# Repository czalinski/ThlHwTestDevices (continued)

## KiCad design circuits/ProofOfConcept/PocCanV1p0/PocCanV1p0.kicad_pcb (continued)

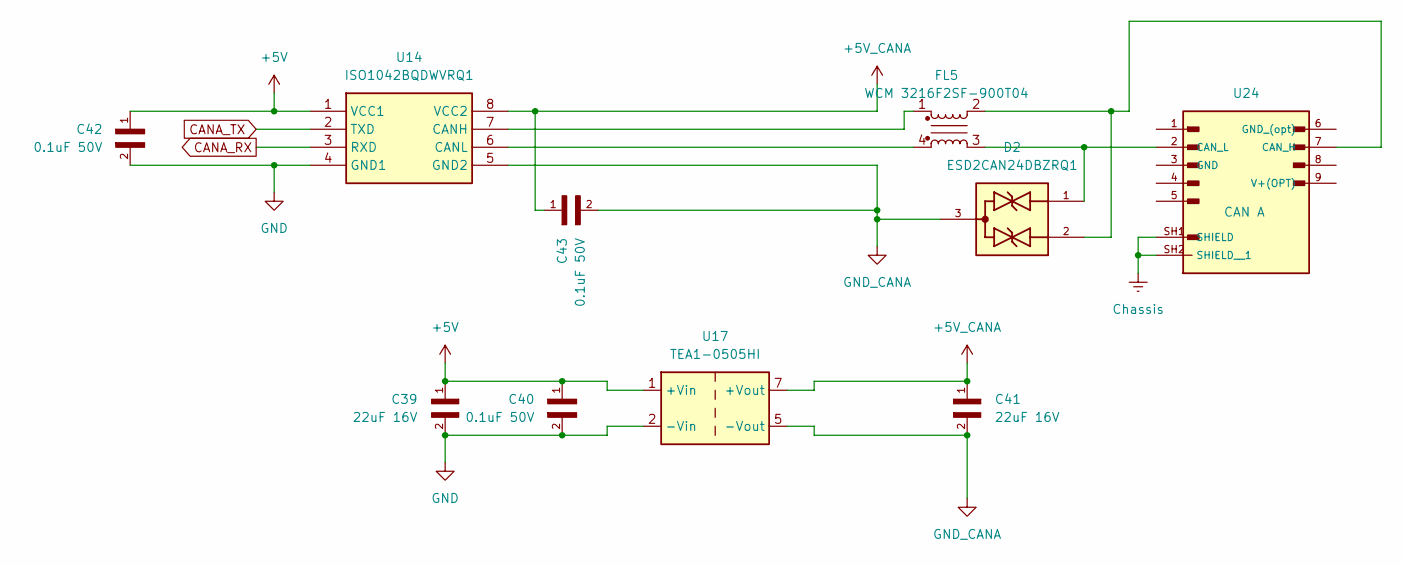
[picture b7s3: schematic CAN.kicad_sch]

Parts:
C39, C41: 22uF 16V; CAPC3216X95N
C40, C42, C43: 0.1uF 50V; CAPC2012X70
D2: ESD2CAN24DBZRQ1; SOT95P237X112-3N; PARTREV C
FL5: WCM 3216F2SF-900T04; WCM 3216F2SF-900T04-1206
U14: ISO1042BQDWVRQ1; SOIC127P1150X280-8N; Manufacturer_Part_Number ISO1042BQDWVRQ1; Mouser Part Number 595-ISO1042BQDWVRQ1
U17: TEA1-0505HI; Converter_DCDC_TRACO_TEA1-xxxxHI_THT
U24: CAN A; ASSMANN_A-DS_09_A_KG-T2S

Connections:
+5V: C39.1, C40.1, C42.1, U14.1 (VCC1), U17.1 (+Vin); also elsewhere on the board
+5V_CANA: C41.1, C43.1, U14.8 (VCC2), U17.7 (+Vout)
CANA_RX: U14.3 (RXD); also elsewhere on the board
CANA_TX: U14.2 (TXD); also elsewhere on the board
Chassis: U24.SH1 (SHIELD), U24.SH2 (SHIELD__1); also elsewhere on the board
GND: C39.2, C40.2, C42.2, U14.4 (GND1), U17.2 (-Vin); also elsewhere on the board
GND_CANA: C41.2, C43.2, D2.3, U14.5 (GND2), U17.5 (-Vout)
unnamed: FL5.1, U14.7 (CANH)
unnamed: FL5.4, U14.6 (CANL)
unnamed: D2.2, FL5.2, U24.7 (CAN_H)
unnamed: D2.1, FL5.3, U24.2 (CAN_L)

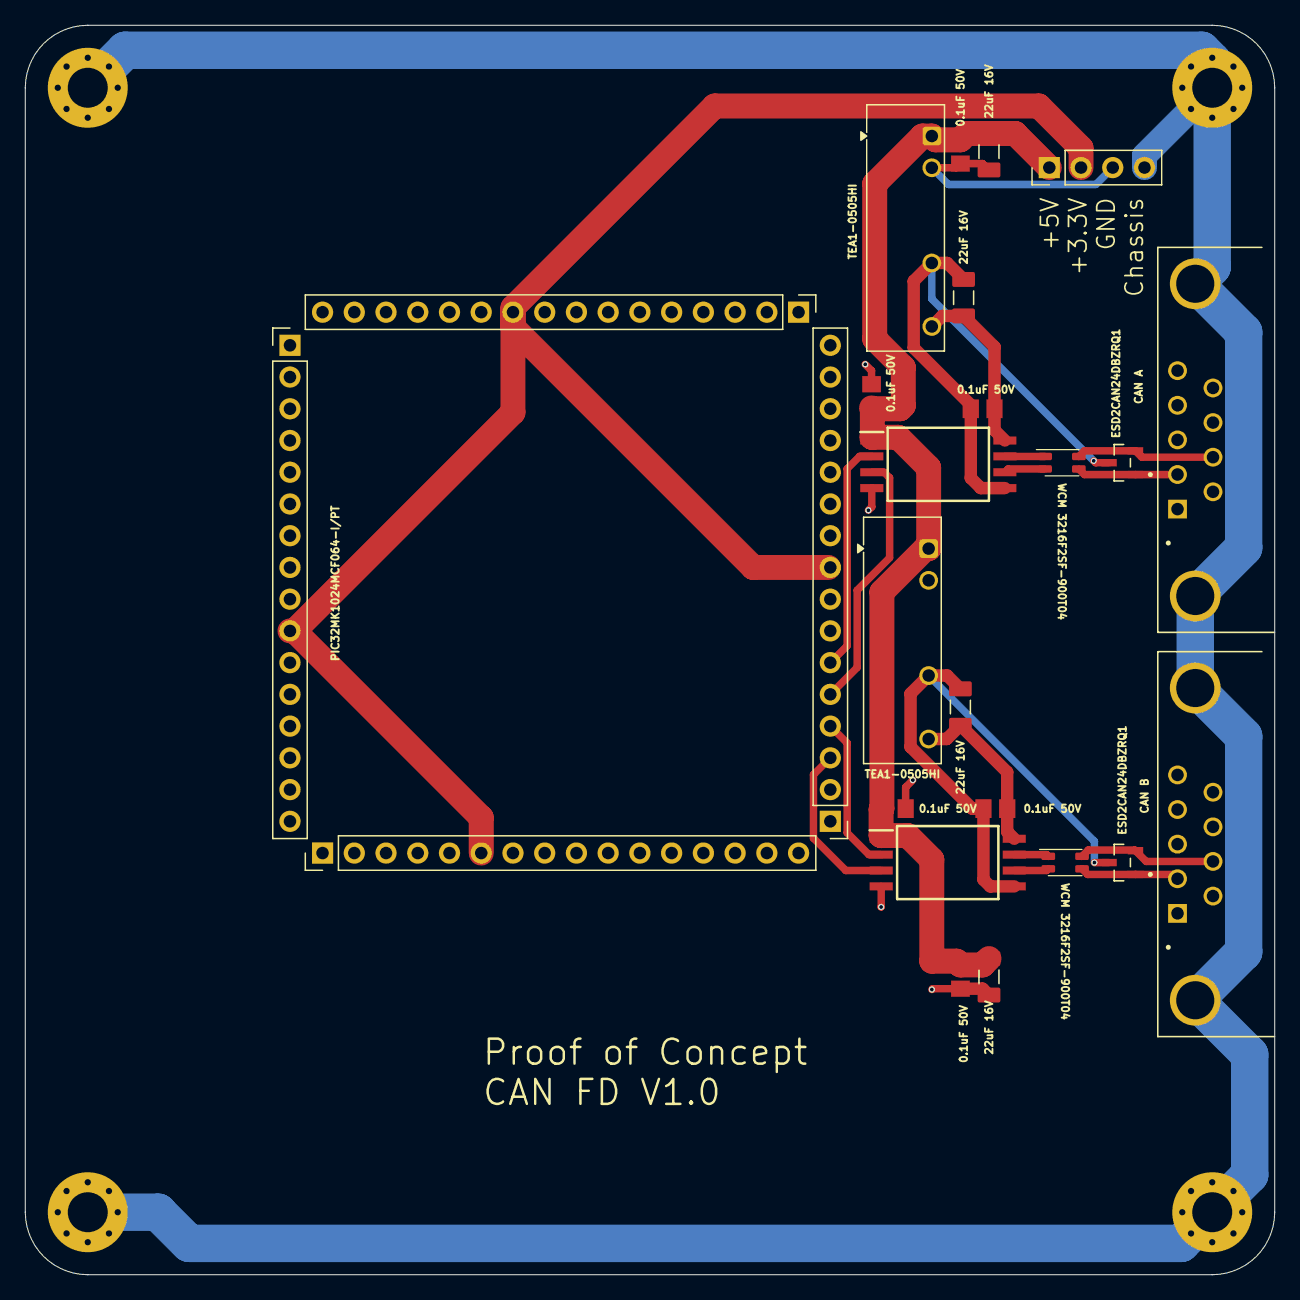
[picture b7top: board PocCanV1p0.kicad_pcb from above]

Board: 2 copper layers, 100.0 x 100.0 mm, 26 parts (0 on the bottom side), 20 nets.

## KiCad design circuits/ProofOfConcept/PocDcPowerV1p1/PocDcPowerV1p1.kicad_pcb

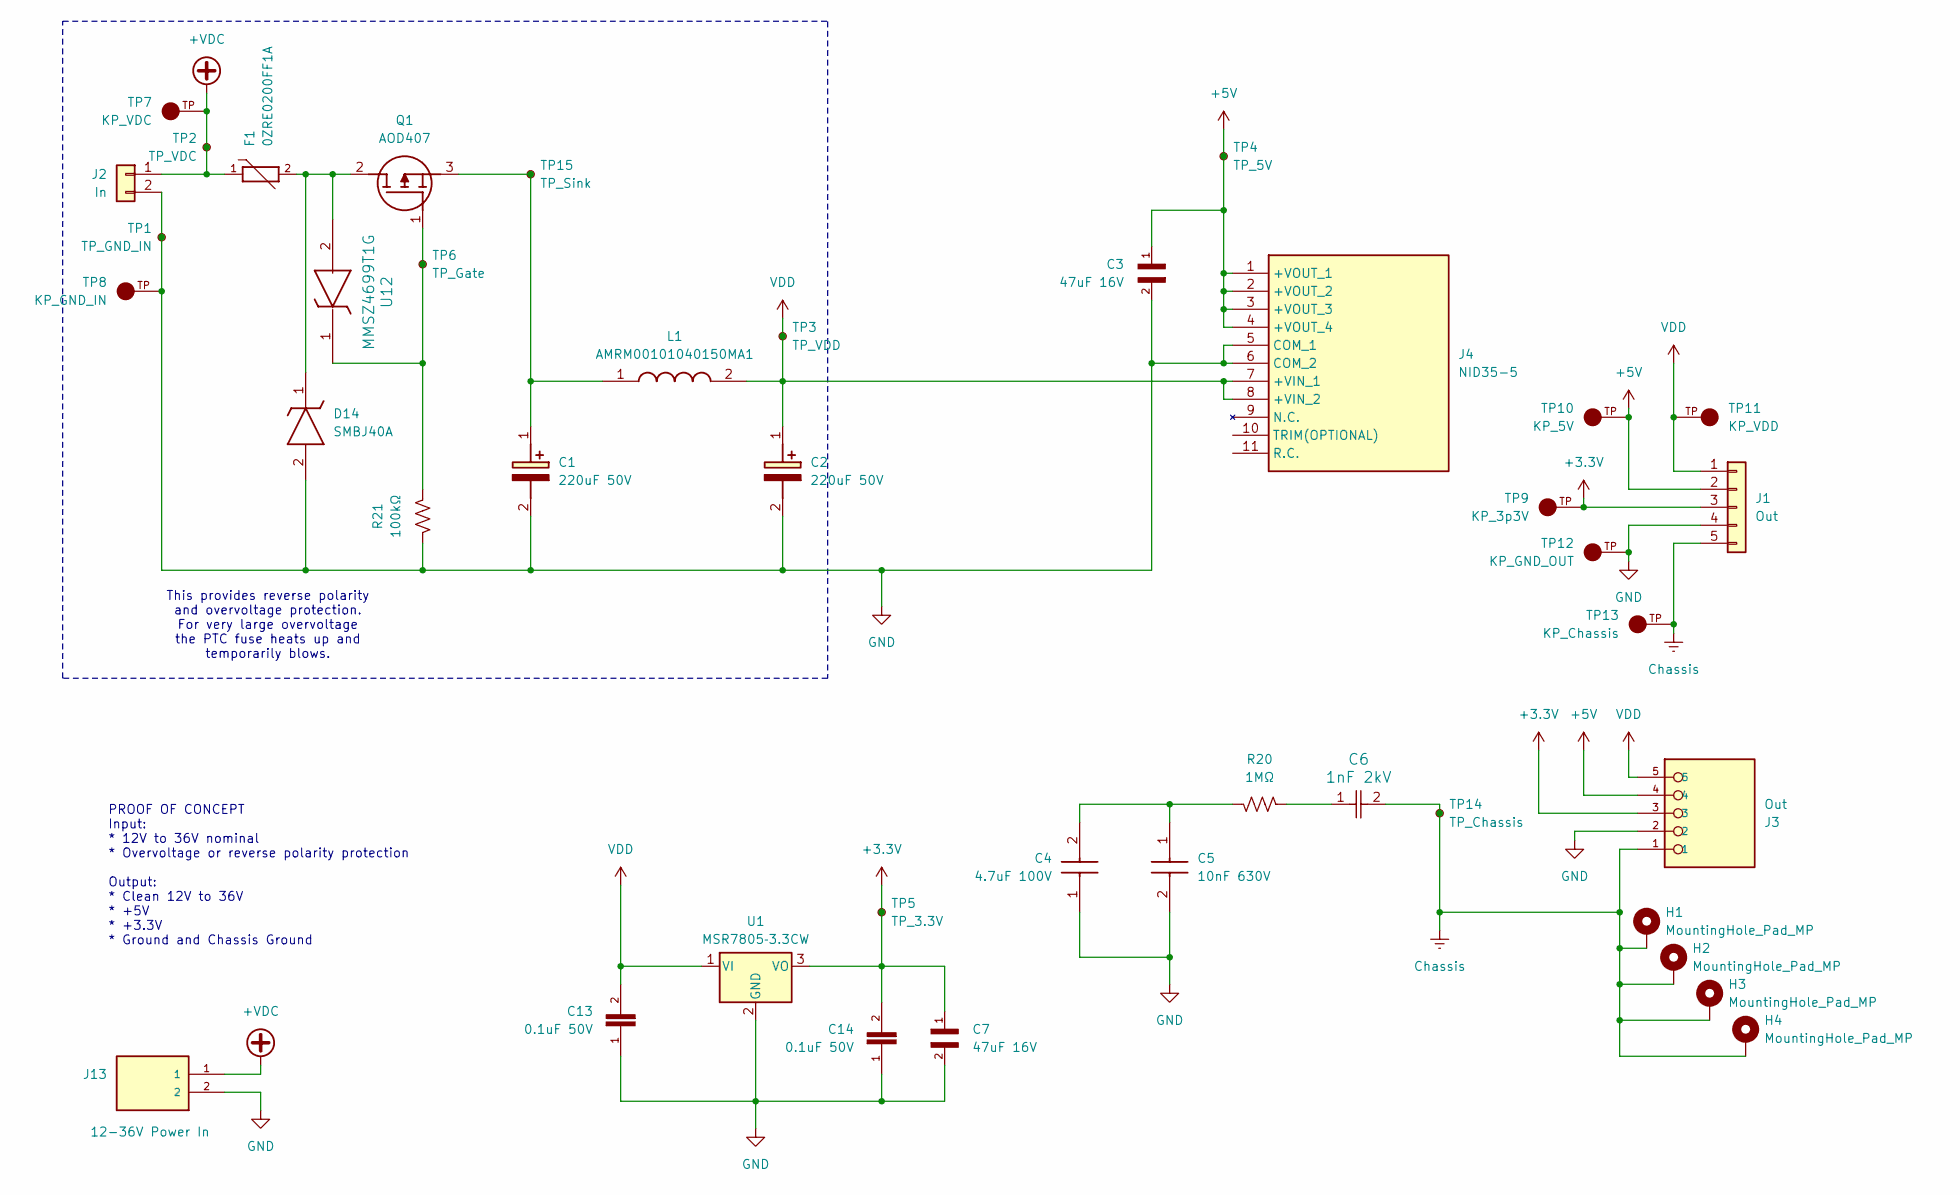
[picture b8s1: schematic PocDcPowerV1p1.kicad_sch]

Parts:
C1, C2: 220uF 50V; CAPPRD500W60D1025H1750; Manufacturer_Part_Number UHE1H221MPD; Mouser Part Number 647-UHE1H221MPD
C3, C7: 47uF 16V; CAPC3225X270N
C4: 4.7uF 100V; GRM31x; Manufacturer_Part_Number GRM31CC72A475ME11K; Mouser Part Number 81-GRM31CC72A475ME1K
C5: 10nF 630V; CAPC3216X135N; Manufacturer_Part_Number 1206B103K631CT
C6: 1nF 2kV; CAPC3216X170N
C13, C14: 0.1uF 50V; CAPC2012X70
D14: SMBJ40A; DIOM5436X265N; Manufacturer_Part_Number SMBJ40A
F1: 0ZRE0200FF1A; FUSRR1020W81L2490T610H3380; PARTREV Apr2023
H1, H2, H3, H4: MountingHole_Pad_MP; MountingHole_3.2mm_M3_Pad_Via
J1: Out; PinHeader_1x05_P2.54mm_Vertical
J2: In; PinHeader_1x02_P2.54mm_Vertical
J3: Out; PHOENIX_1990038
J4: NID35-5; NID355; Manufacturer_Part_Number NID35-5; Mouser Part Number 709-NID35-5
J13: 12-36V Power In; CUI_TB005-762-02BE
L1: AMRM00101040150MA1; INDPM116102X400N; Manufacturer_Part_Number AMRM00101040150MA1
Q1: AOD407; Manufacturer_Part_Number AOD407
R20: 1MΩ; RES_1206
R21: 100kΩ; RES_1206
TP1: TP_GND_IN; TestPoint_Pad_D1.0mm
TP2: TP_VDC; TestPoint_Pad_D1.0mm
TP3: TP_VDD; TestPoint_Pad_D1.0mm
TP4: TP_5V; TestPoint_Pad_D1.0mm
TP5: TP_3.3V; TestPoint_Pad_D1.0mm
TP6: TP_Gate; TestPoint_Pad_D1.0mm
TP7: KP_VDC; KEYSTONE_4954_Slot; PARTREV B; DigiKey_Part_Number 36-4954-ND
TP8: KP_GND_IN; KEYSTONE_4954_Slot; PARTREV B; DigiKey_Part_Number 36-4954-ND
TP9: KP_3p3V; KEYSTONE_4954_Slot; PARTREV B; DigiKey_Part_Number 36-4954-ND
TP10: KP_5V; KEYSTONE_4954_Slot; PARTREV B; DigiKey_Part_Number 36-4954-ND
TP11: KP_VDD; KEYSTONE_4954_Slot; PARTREV B; DigiKey_Part_Number 36-4954-ND
TP12: KP_GND_OUT; KEYSTONE_4954_Slot; PARTREV B; DigiKey_Part_Number 36-4954-ND
TP13: KP_Chassis; KEYSTONE_4954_Slot; PARTREV B; DigiKey_Part_Number 36-4954-ND
TP14: TP_Chassis; TestPoint_Pad_D1.0mm
TP15: TP_Sink; TestPoint_Pad_D1.0mm
U1: MSR7805‑3.3CW; 3-SIP
U12: MMSZ4699T1G; SOD-123_ONS

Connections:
+3.3V: C7.1, C14.2, J1.3, J3.3, TP5.1 (1_1), TP9.TP, U1.3 (VO)
+5V: C3.1, J1.2, J3.4, J4.1 (+VOUT_1), J4.2 (+VOUT_2), J4.3 (+VOUT_3), J4.4 (+VOUT_4), TP4.1 (1_1), TP10.TP
+VDC: F1.1, J2.1, J13.1, TP2.1 (1_1), TP7.TP
Chassis: C6.2, H1.1 (MP_1), H2.1 (MP_1), H3.1 (MP_1), H4.1 (MP_1), J1.5, J3.1, TP13.TP, TP14.1 (1_1)
GND: C1.2 (-), C2.2 (-), C3.2, C4.1, C5.2, C7.2, C13.1, C14.1, D14.2 (A), J1.4, J2.2, J3.2, J4.5 (COM_1), J4.6 (COM_2), J13.2, R21.2, TP1.1 (1_1), TP8.TP, TP12.TP, U1.2 (GND)
unnamed: C1.1 (+), L1.1, Q1.3 (S), TP15.1 (1_1)
unnamed: C4.2, C5.1, R20.2
unnamed: C6.1, R20.1
unnamed: D14.1 (K), F1.2, Q1.2 (D), U12.2
unnamed: Q1.1 (G), R21.1, TP6.1 (1_1), U12.1
VDD: C2.1 (+), C13.2, J1.1, J3.5, J4.7 (+VIN_1), J4.8 (+VIN_2), L1.2, TP3.1 (1_1), TP11.TP, U1.1 (VI)

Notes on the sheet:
PROOF OF CONCEPT Input: * 12V to 36V nominal * Overvoltage or reverse polarity protection Output: * Clean 12V to 36V * +5V * +3.3V * Ground and Chassis Ground
This provides reverse polarity and overvoltage protection. For very large overvoltage the PTC fuse heats up and temporarily blows.

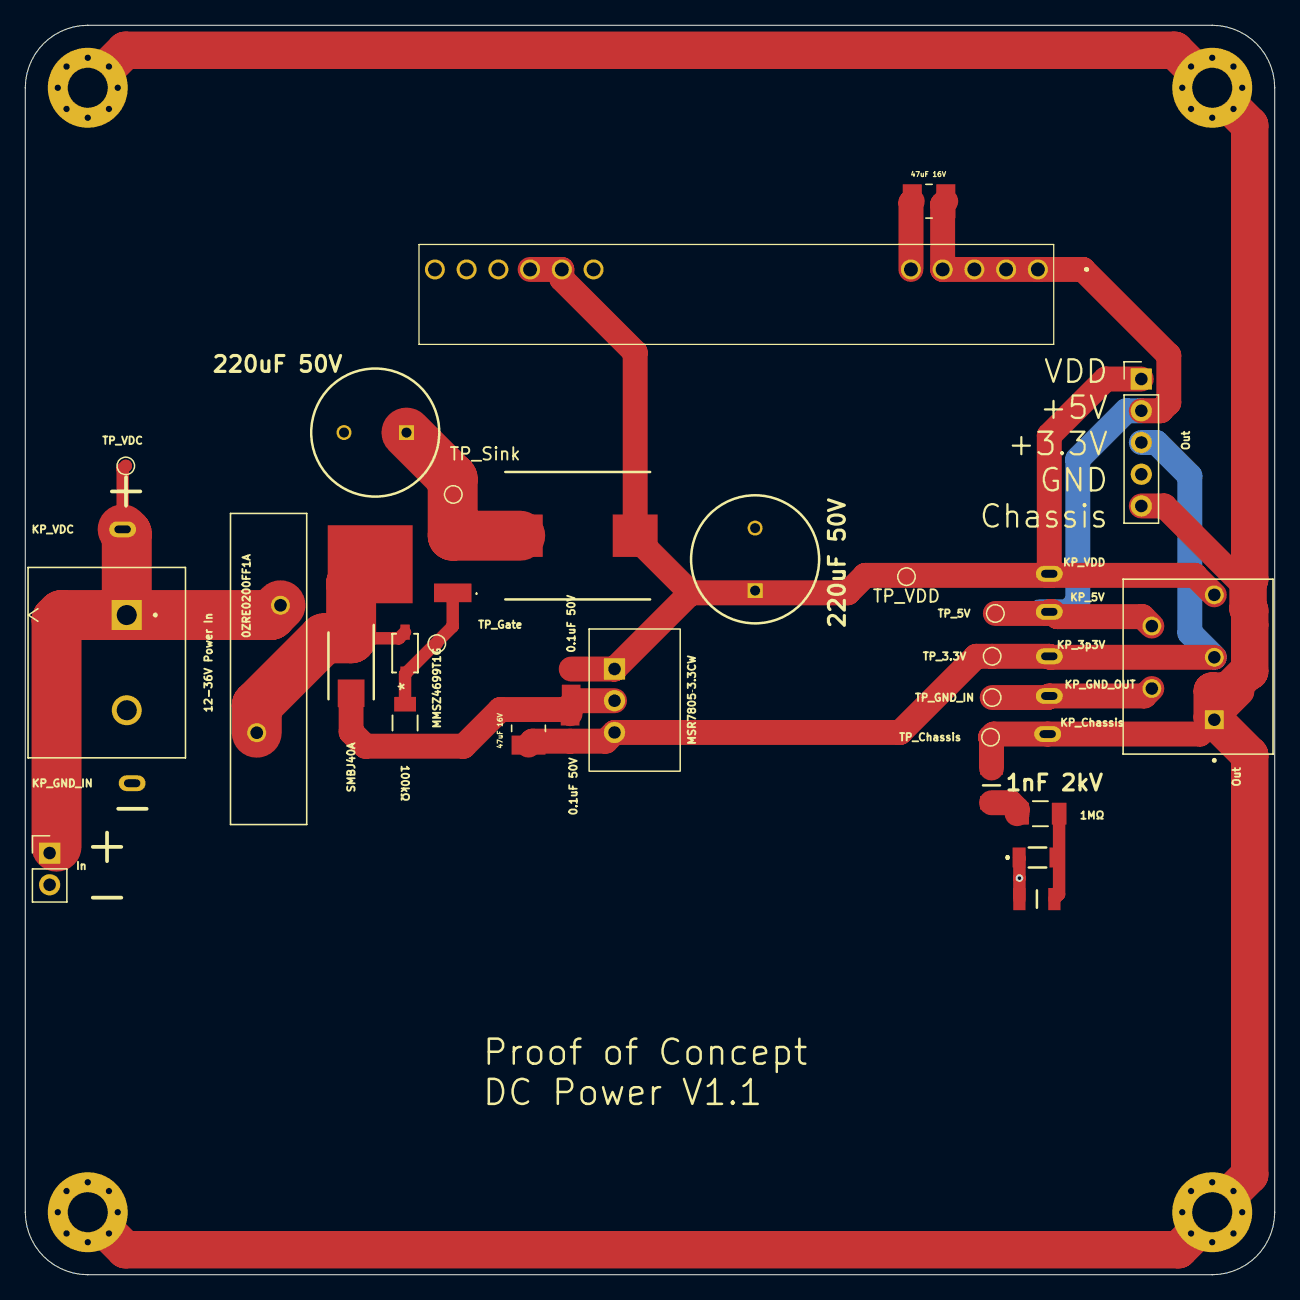
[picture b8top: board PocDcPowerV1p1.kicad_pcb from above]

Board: 2 copper layers, 100.0 x 100.0 mm, 41 parts (0 on the bottom side), 11 nets.
